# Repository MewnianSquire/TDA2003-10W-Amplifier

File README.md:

# TDA2003 10W Amplifier

First try at making a TDA2003 10W amplifier at 12V.

Revisions:
0.1 - The first layout.

Targets:
- Improve circuit layout and reduce PCB size.
- Improve sound quality/frequency response.
- Improve isolation and filtering.
- Add a line / guitar input.
- Add gain control.
- Add EQ. (Don't know if analog or digital EQ)
- Add SFX. (Delay, distortion, etc.)
- Increase Wattage.

Those are my targets to reach in the coming months I hope I can reach them all.

-Mewns

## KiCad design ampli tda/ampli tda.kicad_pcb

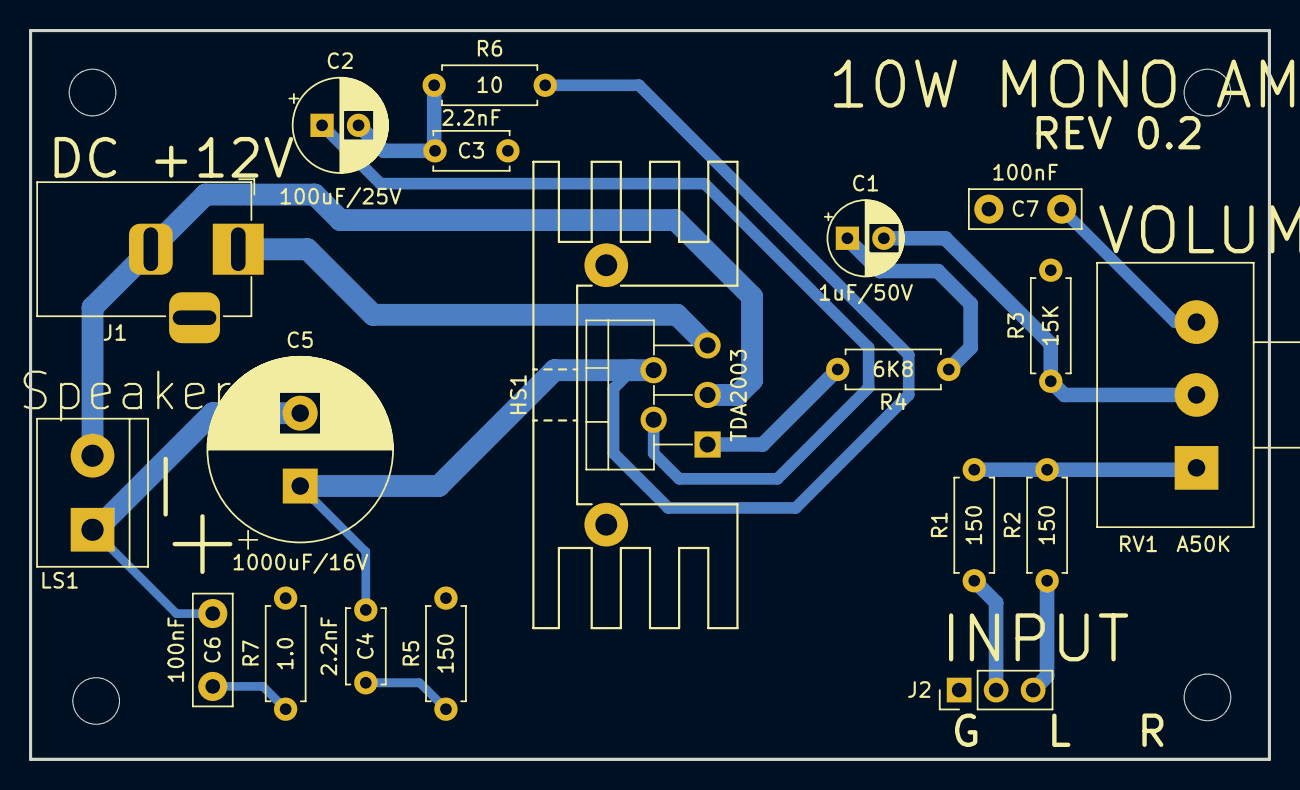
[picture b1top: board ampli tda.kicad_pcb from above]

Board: 2 copper layers, 85.0 x 50.0 mm, 20 parts (0 on the bottom side), 14 nets.

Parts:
C1: 1uF/50V; CP_Radial_D5.0mm_P2.50mm
C2: 100uF/25V; CP_Radial_D6.3mm_P2.50mm
C3, C4: 2.2nF; C_Disc_D5.0mm_W2.5mm_P5.00mm
C5: 1000uF/16V; CP_Radial_D12.5mm_P5.00mm
C6, C7: 100nF; C_Disc_D7.5mm_W2.5mm_P5.00mm
HS1: Heatsink; Heatsink_Stonecold_HS-132_32x14mm_2xFixation1.5mm
J1: Barrel_Jack; BarrelJack_Horizontal
J2: Conn_01x03_Pin; PinHeader_1x03_P2.54mm_Vertical
LS1: Speaker; TerminalBlock_bornier-2_P5.08mm
R1, R2, R5: 150; R_Axial_DIN0207_L6.3mm_D2.5mm_P7.62mm_Horizontal
R3: 15K; R_Axial_DIN0207_L6.3mm_D2.5mm_P7.62mm_Horizontal
R4: 6K8; R_Axial_DIN0207_L6.3mm_D2.5mm_P7.62mm_Horizontal
R6: 10; R_Axial_DIN0207_L6.3mm_D2.5mm_P7.62mm_Horizontal
R7: 1.0; R_Axial_DIN0207_L6.3mm_D2.5mm_P7.62mm_Horizontal
RV1: A50K; Potentiometer_Alps_RK163_Single_Horizontal
U1: TDA2003; TO-220-5_P3.4x3.7mm_StaggerOdd_Lead3.8mm_Vertical

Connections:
GND: C3.2, C7.2, J1.2, J2.1, LS1.2, R3.2, R5.2, R7.2, U1.3 (GND)
unnamed: C1.1, R4.1
unnamed: C1.2, R3.1, RV1.2
unnamed: C2.2, C3.1, C4.2, R5.1, R6.2
unnamed: C4.1, C5.1, R6.1, U1.4
unnamed: C5.2, C6.1, LS1.1
unnamed: C6.2, R7.1
unnamed: C7.1, RV1.3
unnamed: J2.2, R1.1
unnamed: J2.3, R2.1
unnamed: R1.2, R2.2, RV1.1
unnamed: R4.2, U1.1 (+)
unnamed: C2.1, U1.2 (-)
VCC: J1.1, U1.5 (V+)

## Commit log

2023-03-23 First Upload
2023-03-23 Directory change
    Removed unused folders
2023-03-23 REV 0.2
    Update
2023-03-23 REV 0.2
